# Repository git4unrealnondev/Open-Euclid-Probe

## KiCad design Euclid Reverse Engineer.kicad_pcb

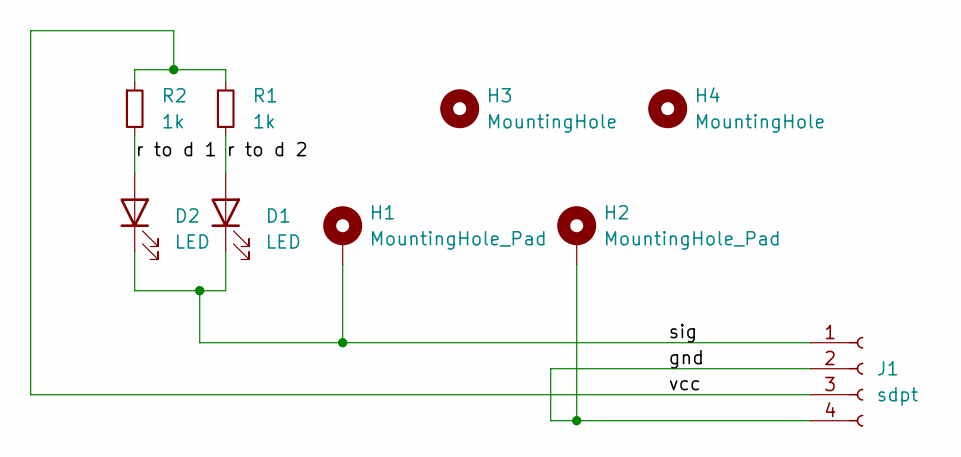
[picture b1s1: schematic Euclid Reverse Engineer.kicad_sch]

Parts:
D1, D2: LED; LED_0603_1608Metric
H1, H2: MountingHole_Pad; MountingHole_3.2mm_M3_Pad_Via
H3, H4: MountingHole; MountingHole_2.1mm
J1: sdpt
R1, R2: 1k; R_0603_1608Metric

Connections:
/gnd: H2.1, J1.2, J1.4
/r to d 1: D2.2 (A), R2.2
/r to d 2: D1.2 (A), R1.2
/sig: D1.1 (K), D2.1 (K), H1.1, J1.1
/vcc: J1.3, R1.1, R2.1

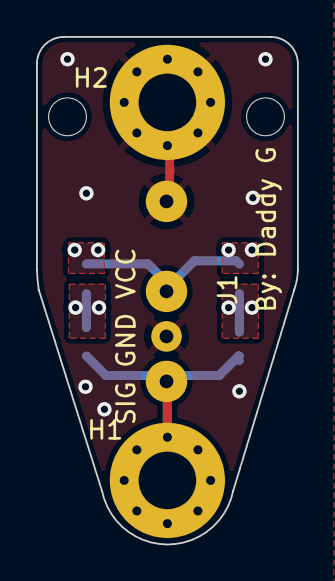
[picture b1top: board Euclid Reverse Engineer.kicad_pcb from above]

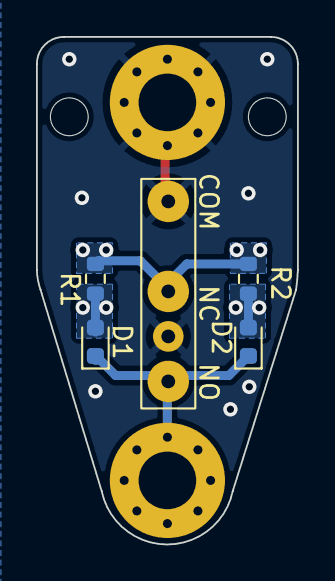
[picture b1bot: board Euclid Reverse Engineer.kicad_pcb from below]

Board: 2 copper layers, 14.5 x 28.2 mm, 9 parts (4 on the bottom side), 5 nets.

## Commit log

2023-02-05 Inital Commit
2023-02-05 Added my name
2023-02-05 Fixing sdpt spacing
2023-02-05 comment
